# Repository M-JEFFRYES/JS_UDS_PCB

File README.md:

# JS_UDS_PCB

This repository store the files required order the PCBs. Please use the latest versions.

Visit the documentation repo for the latest guide [latest urodynamics without borders guide](https://github.com/M-JEFFRYES/JS_UDS_Documentation/blob/main/Urodynamics%20without%20borders%20guide%20(Latest%20Version).pdf).

Visit the [urodynamics without borders](https://urodynamicswithoutborders.com/) website for full project details.

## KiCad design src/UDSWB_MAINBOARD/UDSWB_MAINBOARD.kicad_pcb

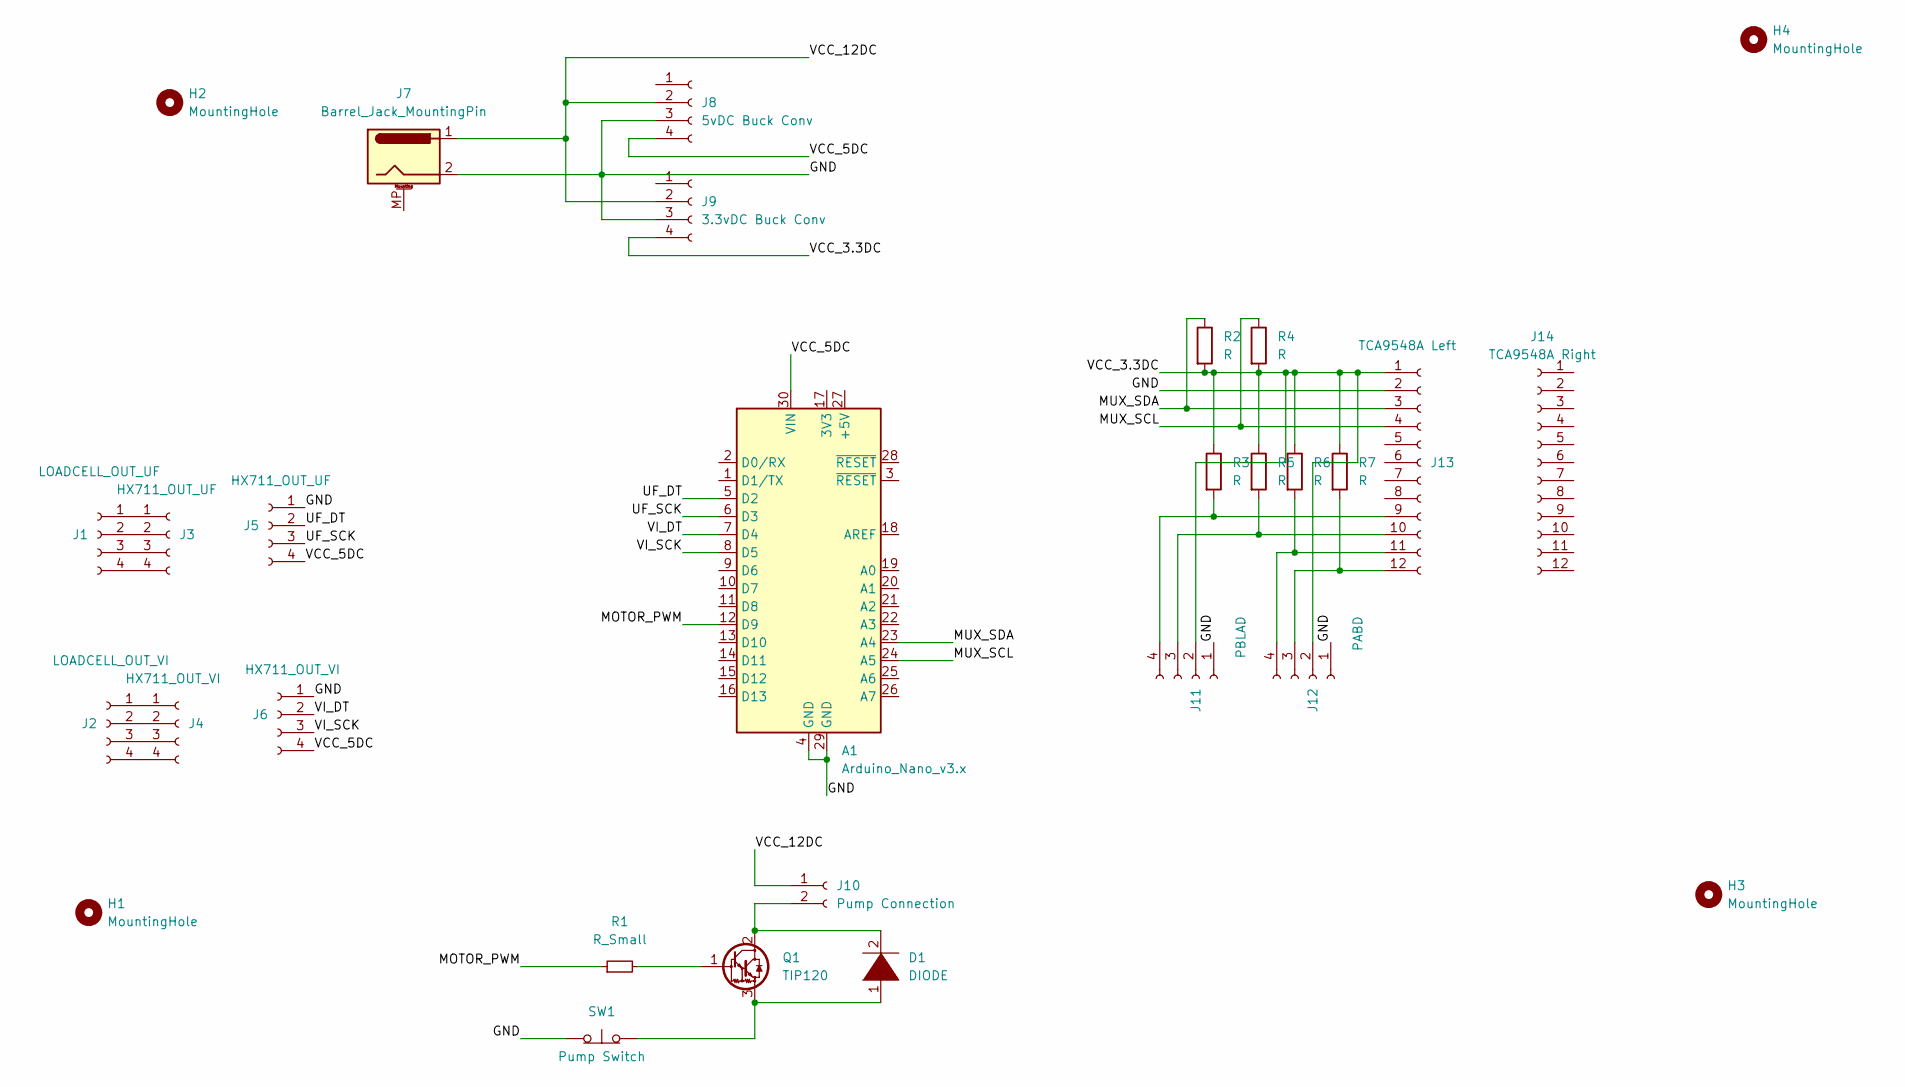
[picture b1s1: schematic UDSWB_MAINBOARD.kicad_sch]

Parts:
A1: Arduino_Nano_v3.x; Arduino_Nano
D1: DIODE; D_5W_P10.16mm_Horizontal
H1, H2, H3, H4: MountingHole; MountingHole_3.7mm
J1: LOADCELL_OUT_UF; PinHeader_1x04_P2.54mm_Vertical
J2: LOADCELL_OUT_VI; PinHeader_1x04_P2.54mm_Vertical
J3, J5: HX711_OUT_UF; PinHeader_1x04_P2.54mm_Vertical
J4, J6: HX711_OUT_VI; PinHeader_1x04_P2.54mm_Vertical
J7: Barrel_Jack_MountingPin; BarrelJack_Horizontal
J8: 5vDC Buck Conv; PinHeader_1x04_P2.54mm_Vertical
J9: 3.3vDC Buck Conv; PinHeader_1x04_P2.54mm_Vertical
J10: Pump Connection; PinHeader_1x02_P2.54mm_Vertical
J11: PBLAD; PinHeader_1x04_P2.54mm_Vertical
J12: PABD; PinHeader_1x04_P2.54mm_Vertical
J13: TCA9548A Left; PinHeader_1x12_P2.54mm_Vertical
J14: TCA9548A Right; PinHeader_1x12_P2.54mm_Vertical
Q1: TIP120; TO-220-3_Vertical
R1: R_Small; R_Axial_DIN0414_L11.9mm_D4.5mm_P15.24mm_Horizontal
R2, R3, R4, R5, R6, R7: R; R_Axial_DIN0414_L11.9mm_D4.5mm_P15.24mm_Horizontal
SW1: Pump Switch; PinHeader_1x02_P2.54mm_Vertical

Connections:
/GND: A1.4 (GND), A1.29 (GND), J5.1, J6.1, J7.2, J8.3, J9.3, J11.1, J12.1, J13.2, SW1.1 (A); also elsewhere on the board
/MOTOR_PWM: A1.12 (D9), R1.1
/MUX_SCL: A1.24 (A5), J13.4, R4.1
/MUX_SDA: A1.23 (A4), J13.3, R2.1
/UF_DT: A1.5 (D2), J5.2
/UF_SCK: A1.6 (D3), J5.3
/VCC_3.3DC: J9.4, J11.2, J12.2, J13.1, R2.2, R3.1, R4.2, R5.1, R6.1, R7.1
/VCC_5DC: A1.30 (VIN), J5.4, J6.4, J8.4
/VCC_12DC: J7.1, J8.2, J9.2, J10.1; also elsewhere on the board
/VI_DT: A1.7 (D4), J6.2
/VI_SCK: A1.8 (D5), J6.3
unnamed 11: D1.1 (K), Q1.3 (E), SW1.2 (B); also elsewhere on the board
unnamed 12: D1.2 (A), J10.2, Q1.2 (C); also elsewhere on the board
unnamed: J1.1, J3.1
unnamed: J1.2, J3.2
unnamed: J1.3, J3.3
unnamed: J1.4, J3.4
unnamed: J2.1, J4.1
unnamed: J2.2, J4.2
unnamed: J2.3, J4.3
unnamed: J2.4, J4.4
unnamed: J11.3, J13.10, R5.2
unnamed: J11.4, J13.9, R3.2
unnamed: J12.3, J13.12, R7.2
unnamed: J12.4, J13.11, R6.2
unnamed: Q1.1 (B), R1.2

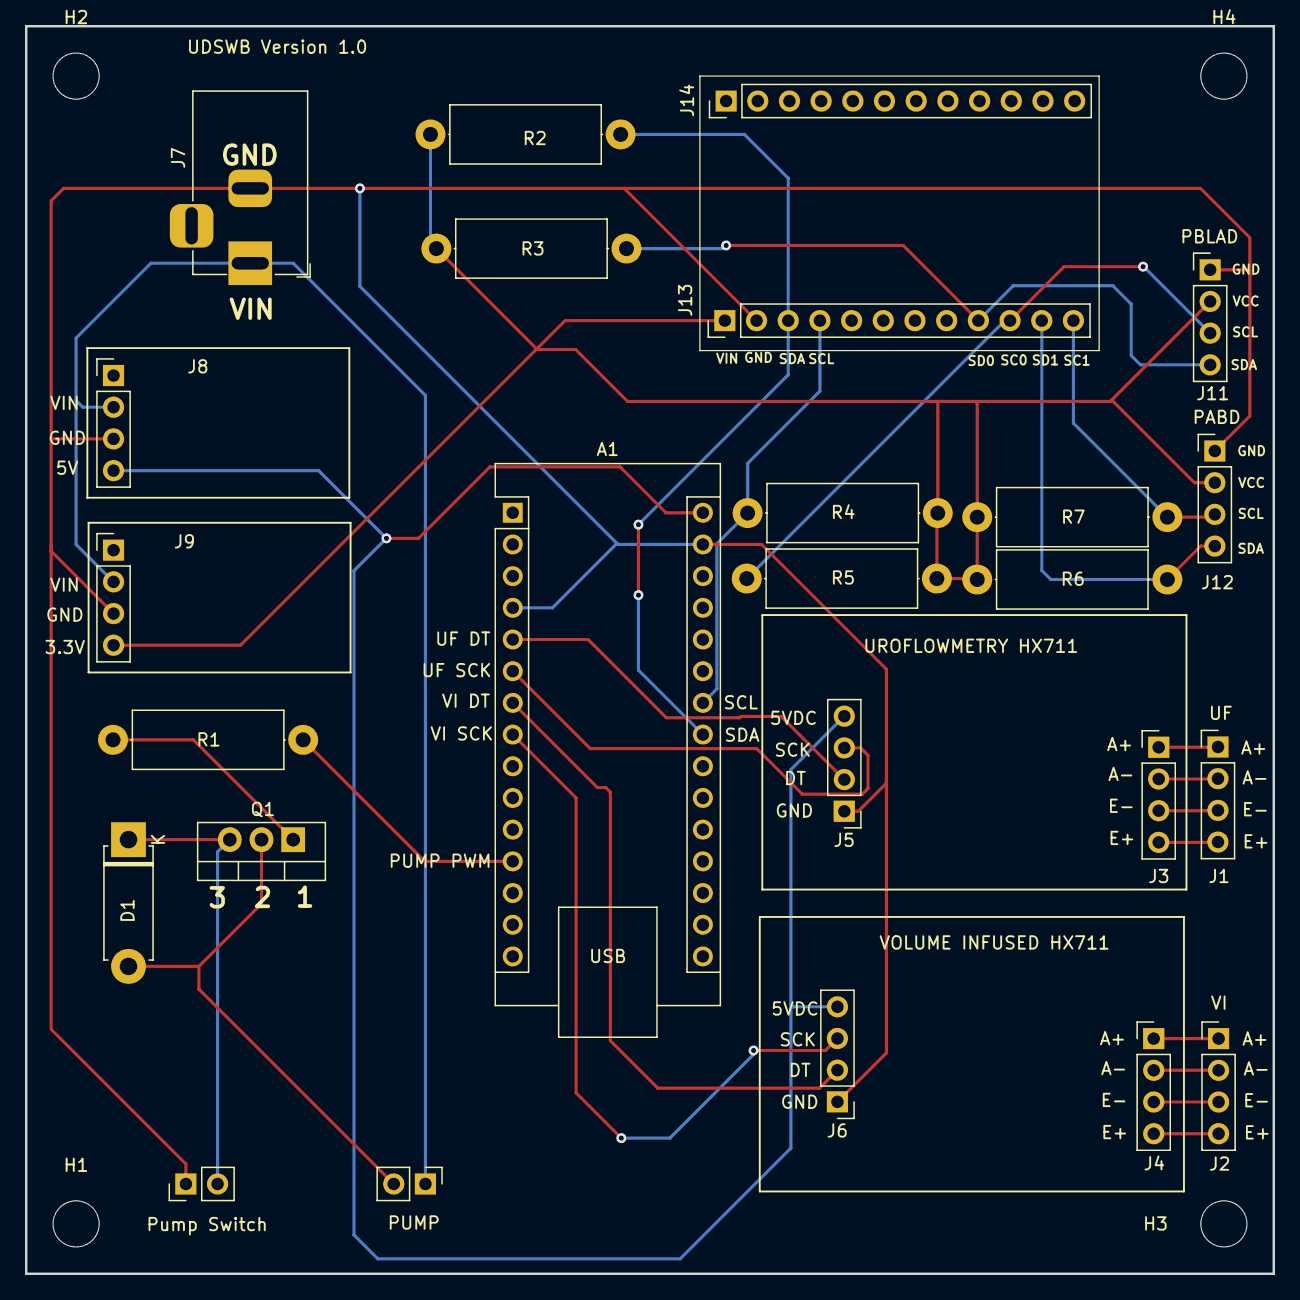
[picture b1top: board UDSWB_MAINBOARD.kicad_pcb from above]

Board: 2 copper layers, 100.0 x 100.0 mm, 29 parts (0 on the bottom side), 26 nets.

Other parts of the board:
PUMP: Pump Connection; PinHeader_1x02_P2.54mm_Vertical
Pump Switch: Pump Switch; PinHeader_1x02_P2.54mm_Vertical

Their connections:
/GND: Pump Switch.1 (A); also elsewhere on the board
/VCC_12DC: PUMP.1; also elsewhere on the board
unnamed 11: Pump Switch.2 (B); also elsewhere on the board
unnamed 12: PUMP.2; also elsewhere on the board

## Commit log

2023-10-06 Add latest dir
2023-10-10 Init files
2023-11-14 Added pad connections
